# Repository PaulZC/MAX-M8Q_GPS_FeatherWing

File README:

###########################
# MAX-M8Q GPS FeatherWing #
###########################

A clone of the Adafruit Ultimate GPS FeatherWing but with the
u-blox MAX-M8Q replacing the GlobalTop FGPMMOPA6H

(PCBs are currently out for manufacture - should be assembled and tested before the end July 2017)

See MAX-M8Q_GPS_FeatherWing.pdf for the BOM etc.:
https://github.com/PaulZC/MAX-M8Q_GPS_FeatherWing/blob/master/MAX-M8Q_GPS_FeatherWing.pdf

The Arduino sub-directory contains code for the Adafruit M0 Feather Adalogger
https://www.adafruit.com/products/2796
which will log your route to SD card in GPX and CSV format

Based on an original design by Adafruit Industries:
https://www.adafruit.com/product/3133
https://github.com/adafruit/Adafruit-Ultimate-GPS-FeatherWing-PCB

Distributed under a Creative Commons Attribution, Share-Alike license

Adafruit invests time and resources providing this open source design,
please support Adafruit and open-source hardware by purchasing products from Adafruit!

Enjoy!

Paul

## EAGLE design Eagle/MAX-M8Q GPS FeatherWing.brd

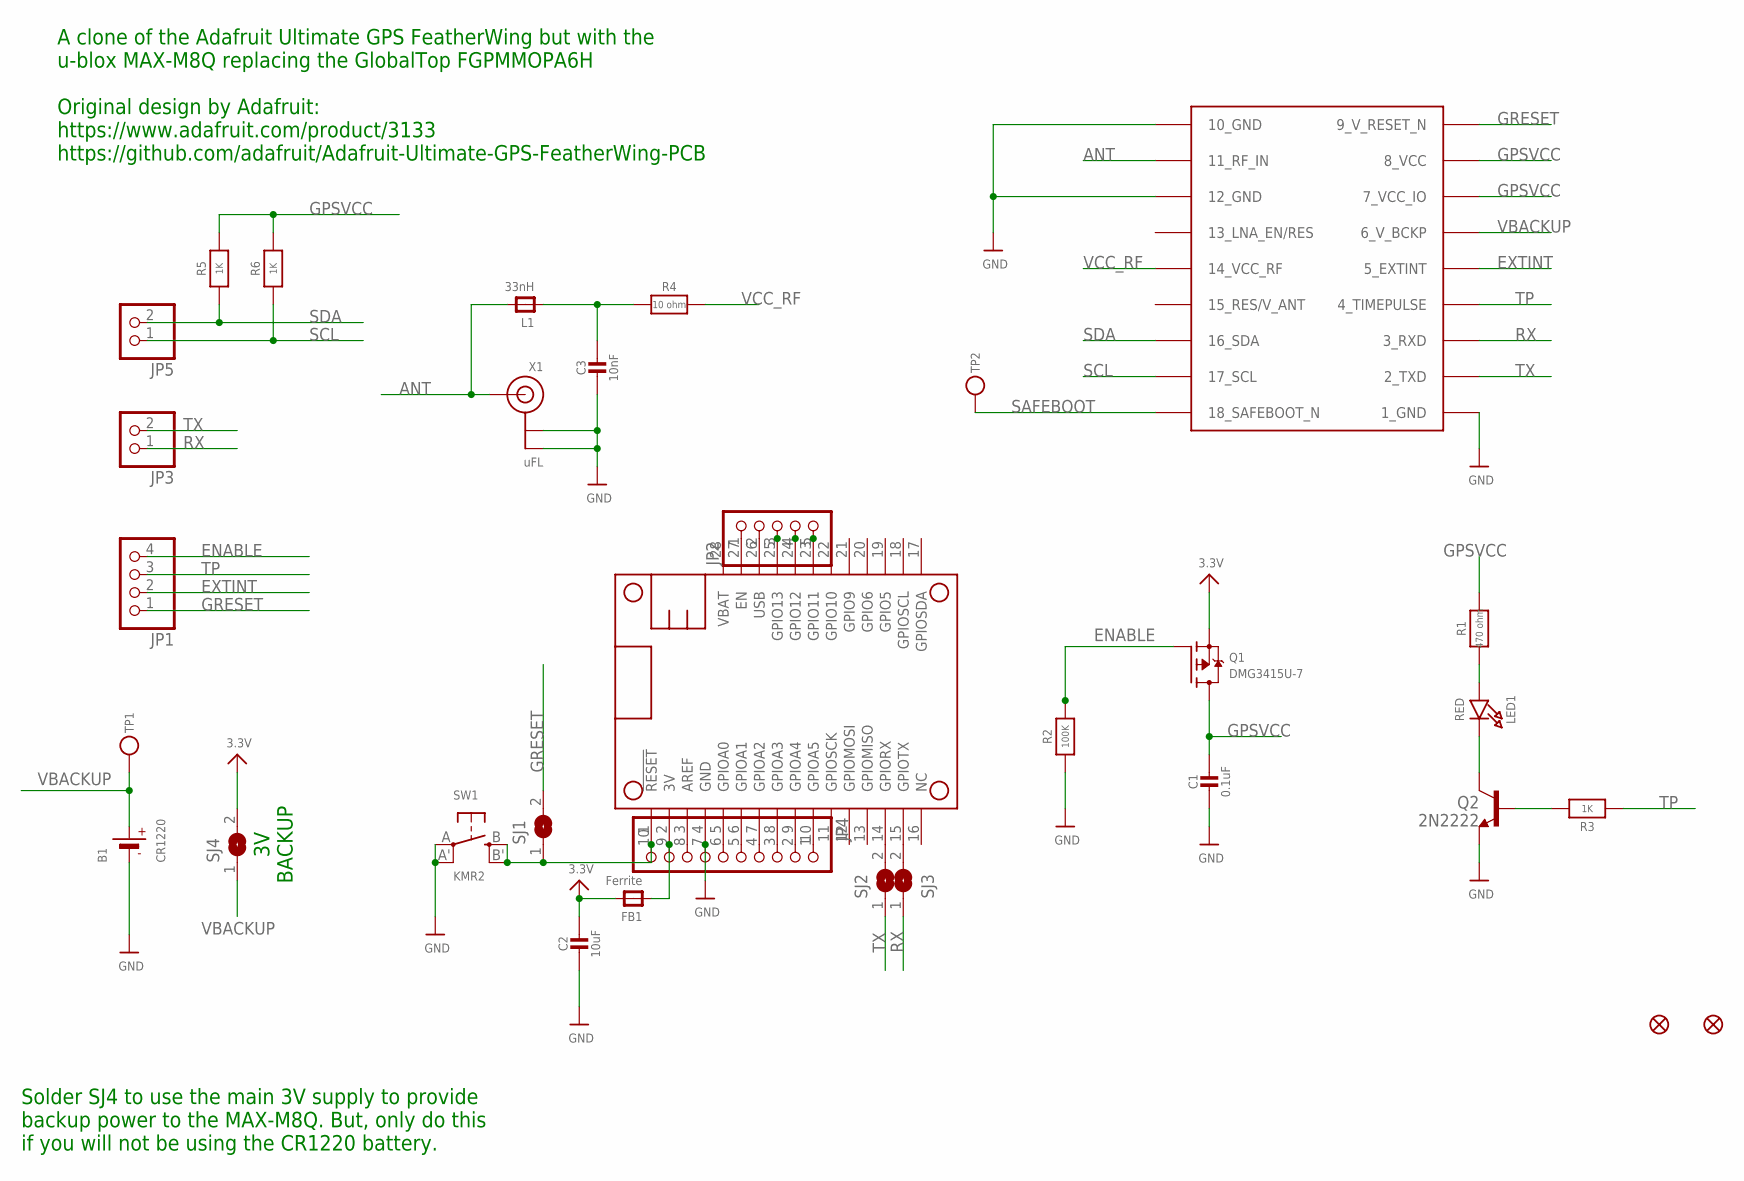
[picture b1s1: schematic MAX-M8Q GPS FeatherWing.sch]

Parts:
B1: CR1220; CR1220-2
C1: 0.1uF; 0805-NO
C2: 10uF; 0805-NO
C3: 10nF; 0805-NO
FB1: Ferrite; 0805-NO
FID1, FID2: FIDUCIAL""; FIDUCIAL_1MM
JP1: HEADER-1X4ROUND; 1X04_ROUND
JP2: HEADER-1X570MIL; 1X05_ROUND_70
JP3, JP5: HEADER-1X2ROUND; 1X02_ROUND
JP4: HEADER-1X10ROUND; 1X10_ROUND
L1: 33nH; 0805-NO
LED1: RED; CHIPLED_0805_NOOUTLINE
MS1: FEATHERWING
Q1: DMG3415U-7; SOT23-WIDE
Q2: 2N2222; SOT23-BEC
R1: 470 ohm; 0805-NO
R2: 100K; 0805-NO
R3, R5, R6: 1K; 0805-NO
R4: 10 ohm; 0805-NO
SJ1, SJ4: SOLDERJUMPER; SOLDERJUMPER_ARROW_NOPASTE
SJ2, SJ3: SOLDERJUMPERCLOSED; SOLDERJUMPER_CLOSEDWIRE
SW1: KMR2; BTN_KMR2_4.6X2.8
TP1, TP2: TESTPOINTROUND1.5MM; TESTPOINT_ROUND_1.5MM
U1: MAX-M8
X1: uFL; U.FL

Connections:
3.3V: C2.1, FB1.2, Q1.2 (S), SJ4.2
3V: FB1.1, JP4.9, MS1.2 (3V)
ANT: L1.2, U1.11_RF_IN, X1.3 (SIGNAL)
ENABLE: JP1.4, Q1.1 (G), R2.2
EXTINT: JP1.2, U1.5_EXTINT
GND: B1.-, C1.2, C2.2, C3.2, JP4.7, MS1.4 (GND), Q2.E, R2.1, SW1.A, SW1.A' (P1), U1.1_GND, U1.10_GND, U1.12_GND, X1.1 (GND), X1.2 (GND)
GPSVCC: C1.1, Q1.3 (D), R1.2, R5.2, R6.2, U1.7_VCC_IO, U1.8_VCC
GRESET: JP1.1, SJ1.2, U1.9_RESET_N (9_V_RESET_N)
unnamed: JP2.3, MS1.25 (GPIO13)
unnamed: LED1.A, R1.1
unnamed: JP2.4, MS1.24 (GPIO12)
unnamed: C3.1, L1.1, R4.1
unnamed: JP2.5, MS1.23 (GPIO11)
unnamed: JP4.1, MS1.10 (GPIOA5)
unnamed: JP4.2, MS1.9 (GPIOA4)
unnamed: JP4.3, MS1.8 (GPIOA3)
unnamed: JP4.4, MS1.7 (GPIOA2)
unnamed: JP4.5, MS1.6 (GPIOA1)
unnamed: JP4.6, MS1.5 (GPIOA0)
unnamed: JP4.10, MS1.1 (!RESET), SJ1.1, SW1.B (S), SW1.B' (S1)
unnamed: JP4.8, MS1.3 (AREF)
unnamed: JP2.1, MS1.27 (EN)
unnamed: MS1.14 (GPIORX), SJ2.2
unnamed: MS1.15 (GPIOTX), SJ3.2
unnamed: LED1.C, Q2.C
unnamed: Q2.B, R3.2
RX: JP3.1, SJ3.1, U1.3_RXD
SAFEBOOT: TP2.P$1, U1.18_SAFEBOOT_N
SCL: JP5.1, R6.1, U1.17_SCL
SDA: JP5.2, R5.1, U1.16_SDA
TP: JP1.3, R3.1, U1.4_TIMEPULSE
TX: JP3.2, SJ2.1, U1.2_TXD
USB: JP2.2, MS1.26 (USB)
VBACKUP: B1.+, SJ4.1, TP1.P$1, U1.6_V_BCKP
VCC_RF: R4.2, U1.14_VCC_RF

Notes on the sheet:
A clone of the Adafruit Ultimate GPS FeatherWing but with the u-blox MAX-M8Q replacing the GlobalTop FGPMMOPA6H Original design by Adafruit: https://www.adafruit.com/product/3133 https://github.com/adafruit/Adafruit-Ultimate-GPS-FeatherWing-PCB
3V BACKUP
Solder SJ4 to use the main 3V supply to provide backup power to the MAX-M8Q. But, only do this if you will not be using the CR1220 battery.

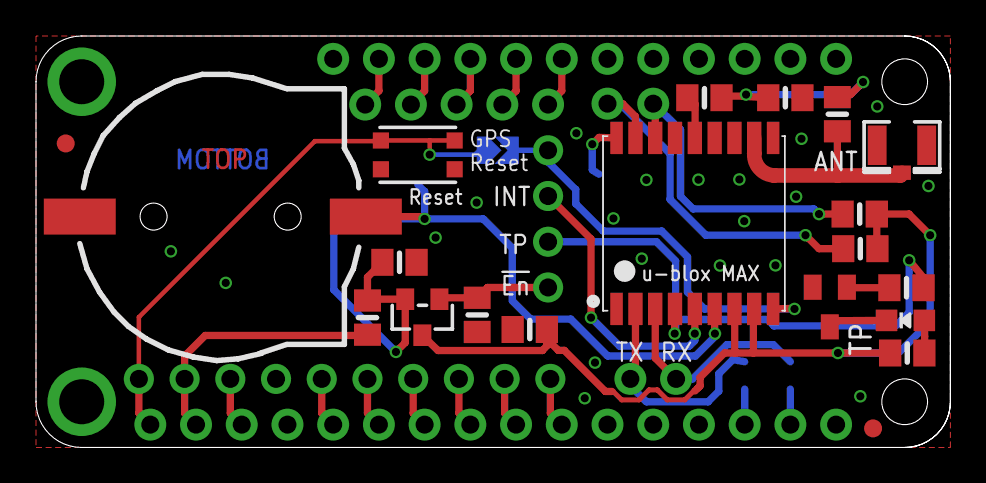
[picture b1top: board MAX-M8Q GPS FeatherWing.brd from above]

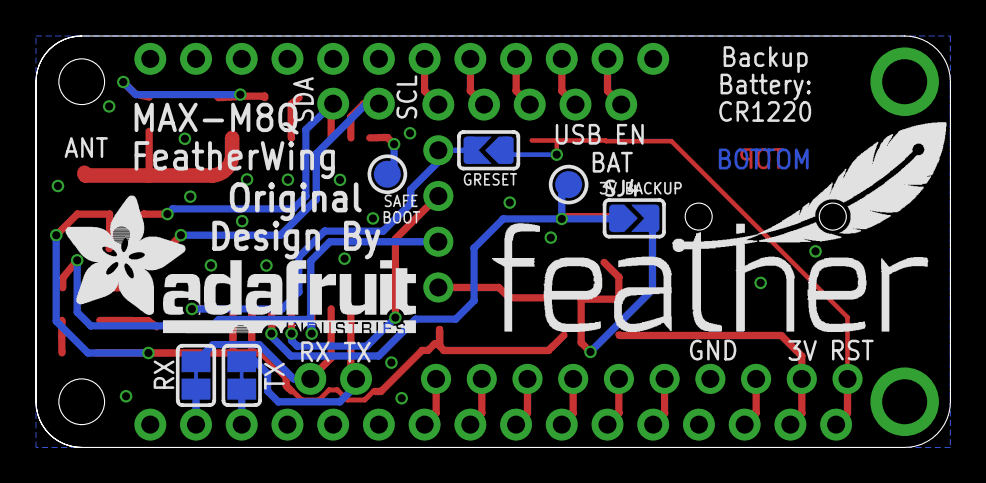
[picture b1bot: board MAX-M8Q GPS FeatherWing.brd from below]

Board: 2 copper layers, 50.8 x 22.9 mm, 32 parts (6 on the bottom side), 35 nets.

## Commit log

2017-06-24 :circus_tent: Added .gitattributes & .gitignore files
2017-06-24 First Release
    A clone of the Adafruit GPS FeatherWing incorporating the u-blox MAX-M8Q
    (external antenna)
2017-06-25 Minor tweaks. Included BOM.
2017-07-06 Updates
    Included the two fiducials in the tCReam layer. Included Arduino code
    which runs on the Adafruit M0 Feather Adalogger which will log your
    route to SD card in GPX and CSV format.
2017-07-17 Tested and working!
    Updated the readme and included images of the tested PCB
2017-08-14 Added HDOP logging
    Arduino code now logs HDOP in both GPX and CSV files
2017-09-05 Updated GPX_and_CSV_Logger to include a stop switch.
2017-09-06 Minor updates
2017-09-20 Updated the Arduino code.
    Updated the Arduino code. sendUBX now calculates the UBX packet
    checksums for you making it much easier to update the M8 configuration.
2017-09-23 Updated PCB
    Updated PCB now includes: pull-up resistors for SCL and SDA; a
    decoupling capacitor for VCC_RF; a test pad for SAFEBOOT.
